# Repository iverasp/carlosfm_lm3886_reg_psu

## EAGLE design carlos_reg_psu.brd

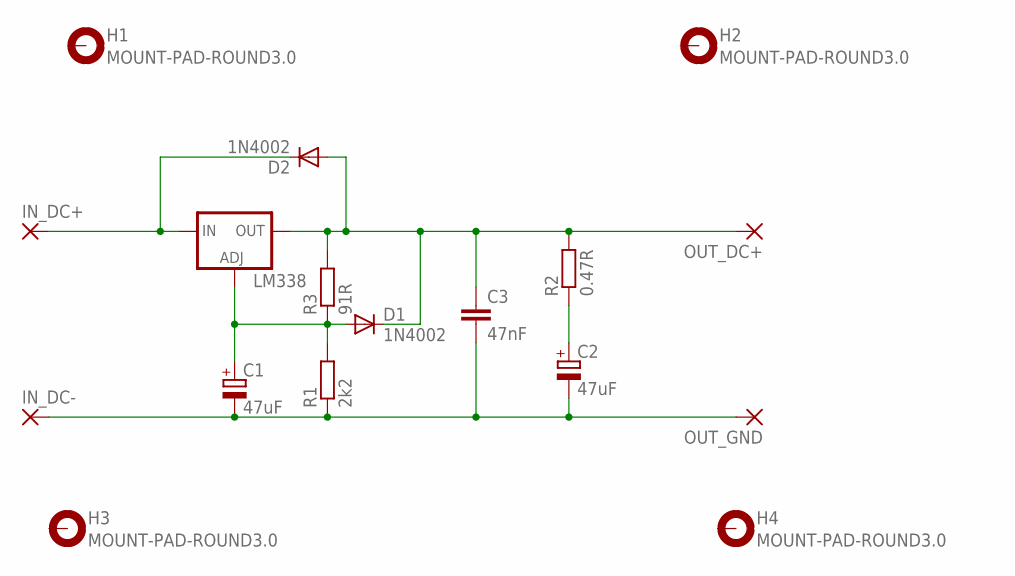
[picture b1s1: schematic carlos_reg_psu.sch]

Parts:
C1, C2: 47uF; E5-13
C3: 47nF; C050-030X075
D1, D2: 1N4002; DO41-10
H1, H2, H3, H4: MOUNT-PAD-ROUND3.0; 3,0-PAD
IN_DC+: 2,54/1,0
IN_DC-: 2,54/1,0
LM338: LM317TS; 317TS
OUT_DC+: 2,54/1,0
OUT_GND: 2,54/1,0
R1: 2k2; 0414V
R2: 0.47R; 0414V
R3: 91R; 0414V

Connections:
unnamed: C2.+, R2.1
unnamed: C1.+, D1.A, LM338.1 (ADJ), R1.2, R3.1
unnamed: C3.1, D1.C, D2.A, LM338.2 (OUT), OUT_DC+.1, R2.2, R3.2
unnamed: D2.C, IN_DC+.1, LM338.3 (IN)
unnamed: C1.-, C2.-, C3.2, IN_DC-.1, OUT_GND.1, R1.1

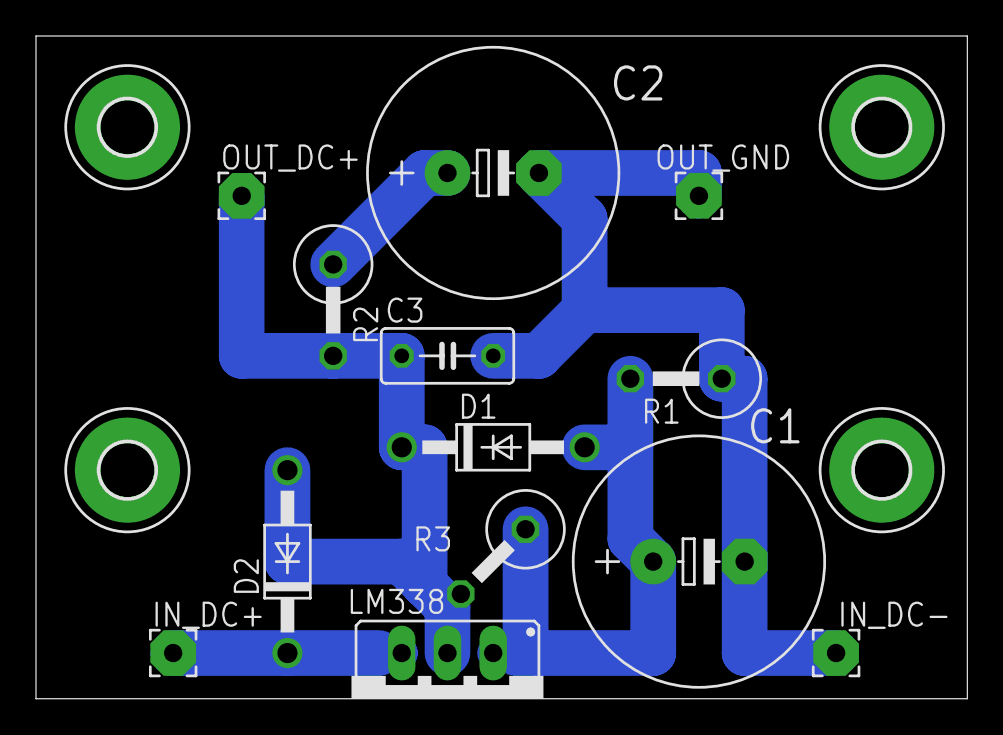
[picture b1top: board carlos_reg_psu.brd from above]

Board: 2 copper layers, 51.7 x 36.8 mm, 17 parts (0 on the bottom side), 5 nets.

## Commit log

2015-10-27 added schematic
2015-10-27 added eagle schematic
2015-10-27 rev0 finished
2015-10-27 minor placement fix
2015-10-29 moved current set resistor closer to output as described in datasheet
